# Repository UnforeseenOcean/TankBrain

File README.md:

# TankBrain
Official repository for TankBrain, a replacement board for Academy and other motorized vehicle models

# What is this?
This is an Arduino-compatible* board with remote controller that replaces either the old 30/40MHz band remote control or wired remote on models from Academy Plastic Models or other companies.
Currently it supports Academy's wired motorized tank models (the benchmark being their ROK K1A1 tank model), but with some support it should be easy to make it support nearly all models.

\*: Arduino-compatible in this context means "Arduino IDE compatible". The board in no way, shape or form can support peripherals made for Arduino Uno and other boards.

# Goals
- To create a universal board that fits into most models, including some toy vehicles (such as tanks or cars)
- To make a firmware that handles most functions called by signals through 433MHz ASK/OOK module

# Information
This board currently uses GoodRF SRX887 and STX887 pair, which has a good range of operation with least amount of latency (due to it not containing any signal-to-binary conversion) from the online reviews.

The operating state table is as follows:
```
ABCD (AIN1,AIN2,BIN1,BIN2)
0000 (Stop)
0001 (Backwards Left Strafe)
0010 (Right Strafe)
0011 (Invalid/Unused)
0100 (Backwards Right Strafe)
0101 (Backward)
0110 (Right Turn In Place)
0111 (Invalid/Unused)
1000 (Left Strafe)
1001 (Left Turn In Place)
1010 (Forward)
1011 (Invalid/Unused)
1100 (Invalid/Unused)
1101 (Invalid/Unused)
1110 (Invalid/Unused)
1111 (Brake)
```
Simulation for engine starting and firing is handled by switching the movement state through this table:
```
1010 (Start of "Engine start" movement set)
0101
1010
0101
1010
0101 (Start of "Fire" movement set)
1010
0101
1111
0000 (End)
```
There is a plan to add support for external sound modules (DFPlayer Mini / Serial MP3 player modules)

The board needs some revision and quality/function check, as it has not been made yet. However this is what the board could look like if the current design is made:

Believe it or not this is the second big revision -- the first one was... not good.

# Credits
Pololu - DRV8833 circuit design

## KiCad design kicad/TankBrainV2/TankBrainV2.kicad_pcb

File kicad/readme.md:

# KiCad project files
Yes, they're here. Please make improvements to this, since I have no idea if this is going to do the job or not!

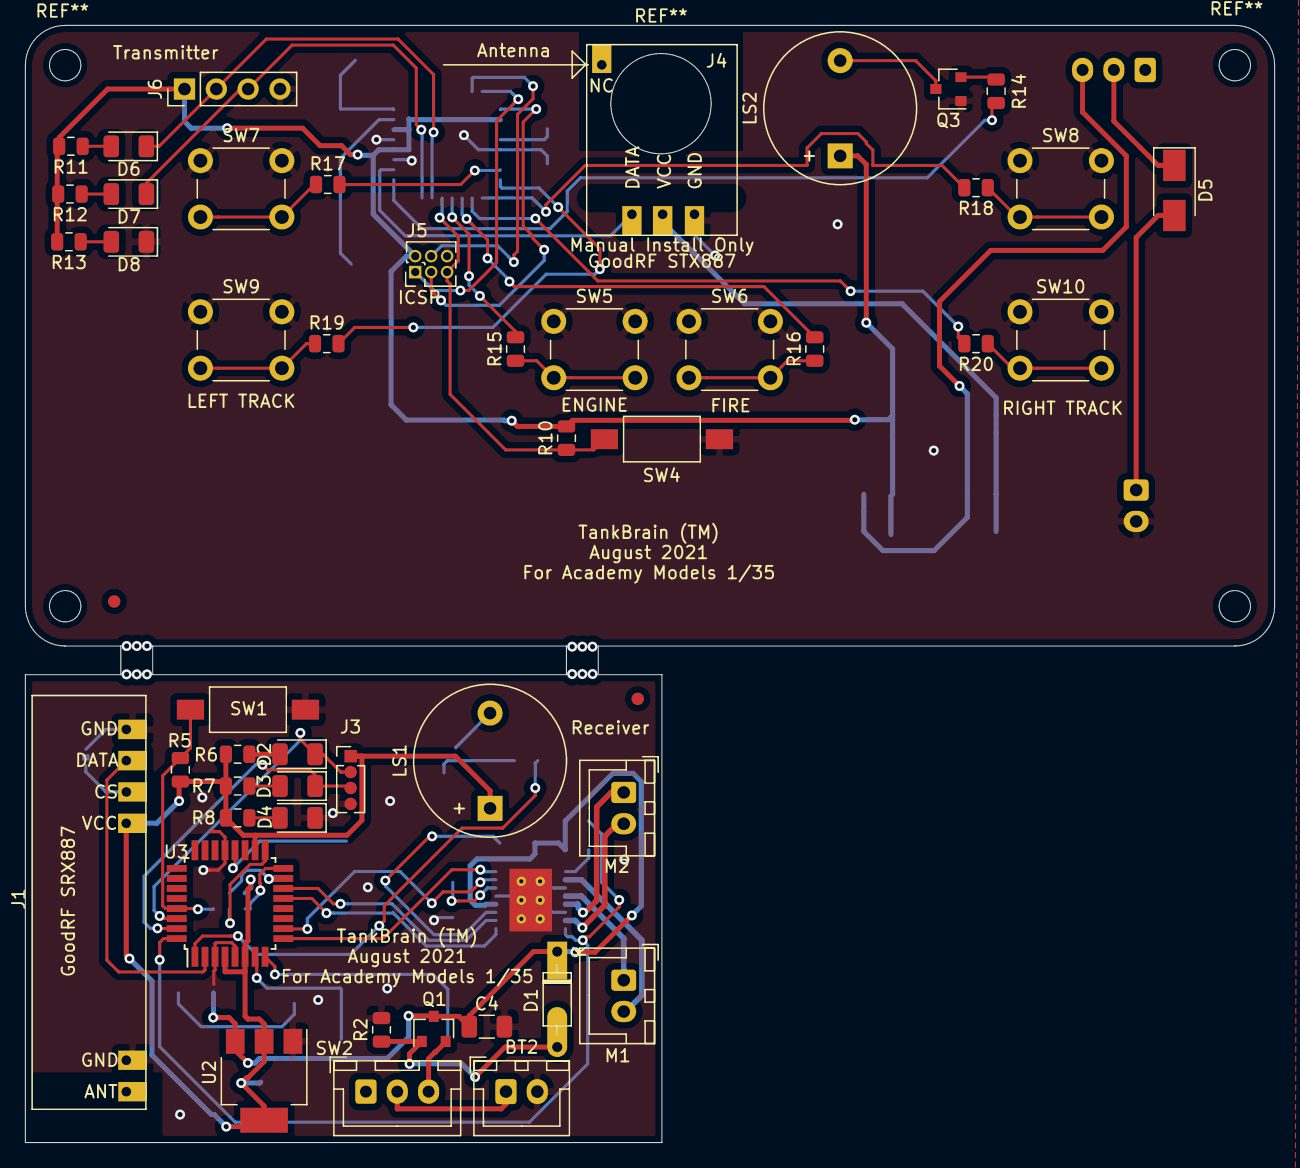
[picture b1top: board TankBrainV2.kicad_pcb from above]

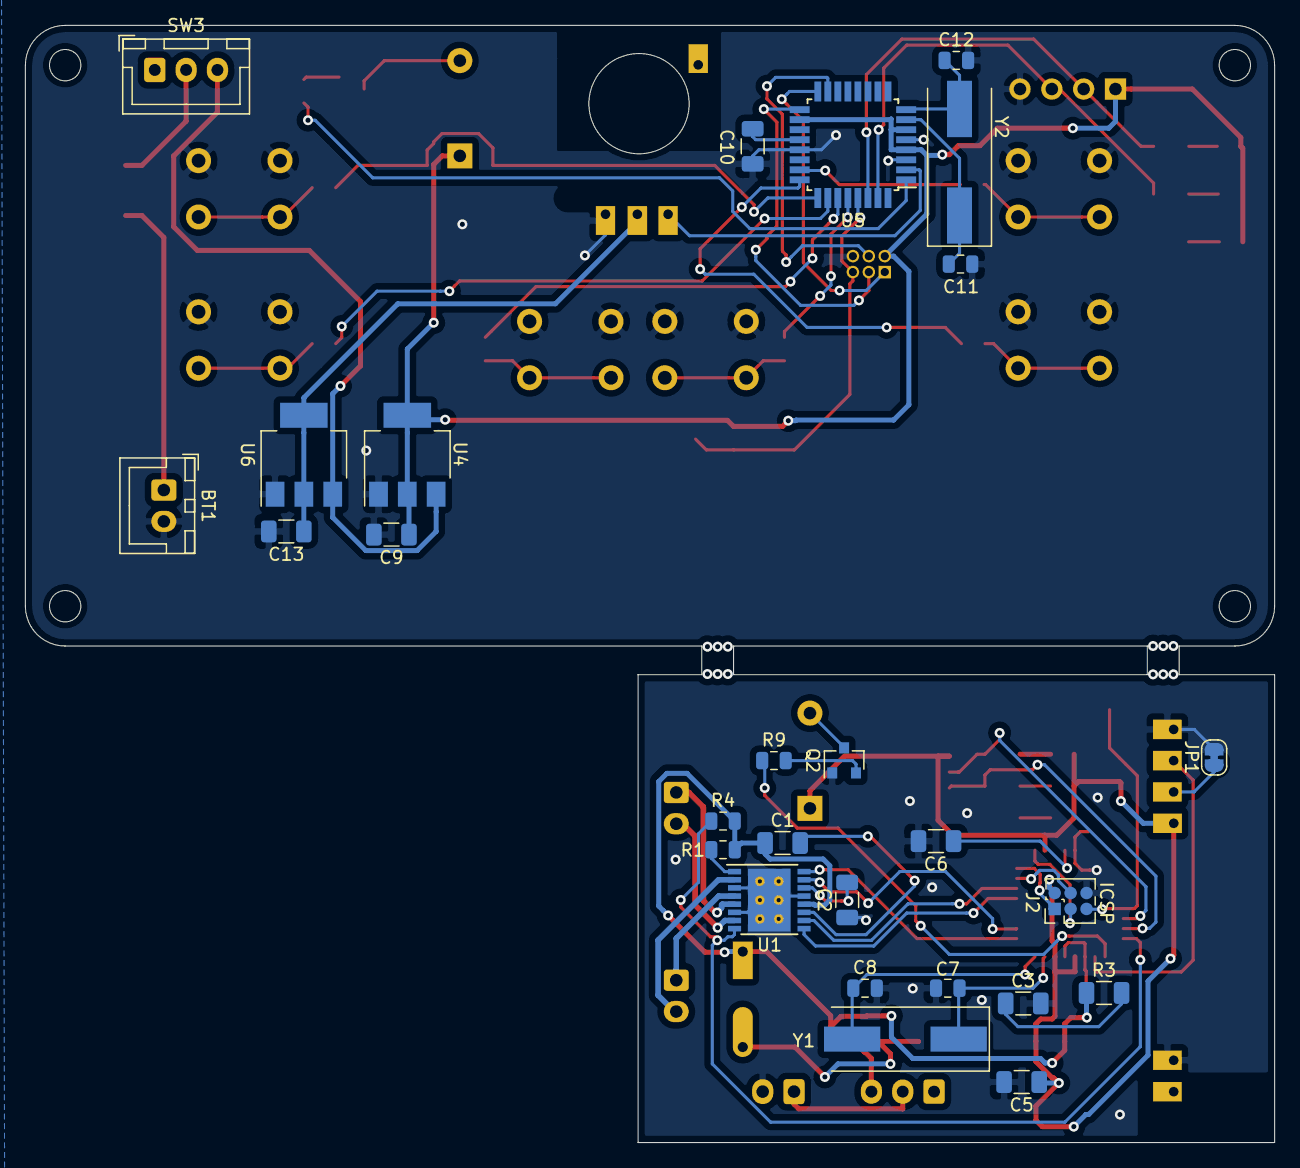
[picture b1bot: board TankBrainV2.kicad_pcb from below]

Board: 2 copper layers, 99.7 x 89.2 mm, 75 parts (27 on the bottom side), 69 nets.

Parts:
BT1: 9V; JST_XH_B2B-XH-A_1x02_P2.50mm_Vertical
BT2: 4.3V; JST_XH_B2B-XH-A_1x02_P2.50mm_Vertical
C1, C4, C5, C6, C9, C10, C13: 100nF; C_1206_3216Metric
C2: 2.2uF; C_1206_3216Metric
C3: 10uF; C_1206_3216Metric
C7, C8, C11, C12: 22nF; C_0805_2012Metric
D1: 6.8V; D_DO-35_SOD27_P7.62mm_Horizontal
D2, D6: RX; LED_1206_3216Metric
D3, D7: TX; LED_1206_3216Metric
D4, D8: PWR; LED_1206_3216Metric
D5: 1N4001; D_SMA
J1: 433RX; SRX887
J2, J5: ISP; PinHeader_2x03_P1.27mm_Vertical
J3: UART; PinHeader_1x04_P1.27mm_Vertical
J4: 433TX; STX887
J6: UART; PinHeader_1x04_P2.54mm_Vertical
JP1: GRF; SolderJumper-2_P1.3mm_Bridged_RoundedPad1.0x1.5mm
LS1, LS2: Speaker; Buzzer_12x9.5RM7.6
M1: L; JST_XH_B2B-XH-A_1x02_P2.50mm_Vertical
M2: R; JST_XH_B2B-XH-A_1x02_P2.50mm_Vertical
Q1: AO3401; SOT-23
Q2, Q3: 2N3904; SOT-23
R1, R4: 47K; R_0805_2012Metric
R2: 100K; R_0805_2012Metric
R3: 1R; R_1206_3216Metric
R5, R10: 10K; R_0805_2012Metric
R6, R7, R8, R9, R11, R12, R13, R14, R15, R16, R17, R18, R19, R20: 1K; R_0805_2012Metric
SW1, SW4: RESET; SW_SPST_FSMSM
SW2: POWER_RX; JST_XH_B3B-XH-A_1x03_P2.50mm_Vertical
SW3: POWER_TX; JST_XH_B3B-XH-A_1x03_P2.50mm_Vertical
SW5: ENGINE; SW_PUSH_6mm
SW6: FIRE; SW_PUSH_6mm
SW7: UP_LEFT; SW_PUSH_6mm
SW8: UP_RIGHT; SW_PUSH_6mm
SW9: DOWN_LEFT; SW_PUSH_6mm
SW10: DOWN_RIGHT; SW_PUSH_6mm
U1: DRV8833PWP; HTSSOP-16-1EP_4.4x5mm_P0.65mm_EP3.4x5mm_Mask2.46x2.31mm_The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
U2, U6: AMS1117-3.3; SOT-223-3_TabPin2
U3, U5: ATmega328P-AU; TQFP-32_7x7mm_P0.8mm
U4: AMS1117-5.0; SOT-223-3_TabPin2
Y1: 8MHz; Crystal_SMD_HC49-SD
Y2: 16MHz; Crystal_SMD_HC49-SD

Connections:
A1: U1.16, U3.9
A2: U1.15, U3.10
B1: U1.9, U3.13
B2: U1.10, U3.14
BUZZER: R9.1, U3.1
BZR: R14.1, U5.1
CK: J5.3, U5.17
ENGINE: R15.2, U5.28
FAULT: R4.1, U1.8, U3.32
FIRE: R16.2, U5.27
GND: BT1.2, BT2.2, C2.1, C3.2, C4.2, C5.2, C6.2, C7.2, C8.2, C9.2, C10.2, C11.2, C12.2, C13.2, D4.1, D8.1, J1.2, J1.6, J2.6, J3.4, J4.4, J5.6, J6.4, JP1.2, Q2.1, Q3.1, R2.2, SW1.2, SW4.2, SW5.1, SW6.1, SW7.1, SW8.1, SW9.1, SW10.1, U1.3, U1.6, U1.13, U1.17, U2.1, U3.3, U3.5, U3.21, U4.1, U5.3, U5.5, U5.21, U6.1
LO1: M1.2, U1.2
LO2: M1.1, U1.4
LSWD: R19.2, U5.24
LSWU: R17.2, U5.23
MI: J5.1, U5.16
MISO: J2.1, U3.16
MO: J5.4, U5.15
MOSI: J2.4, U3.15
unnamed: BT1.1, D5.2
unnamed: C1.2, U1.11
unnamed: C2.2, U1.14
unnamed: C3.1, R3.2
unnamed: C6.1, U3.20
unnamed: C7.1, U3.7, Y1.1
unnamed: C8.1, U3.8, Y1.2
unnamed: C10.1, U5.20
unnamed: C11.1, U5.7, Y2.1
unnamed: C12.1, U5.8, Y2.2
unnamed: C13.1, J4.3, U6.2
unnamed: D1.2, Q1.1, R2.1
unnamed: D2.2, R6.1
unnamed: D3.2, R7.1
unnamed: D4.2, R8.1
unnamed: D5.1, SW3.2
unnamed: D6.2, R11.1
unnamed: D7.2, R12.1
unnamed: D8.2, R13.1
unnamed: J1.4, JP1.1
unnamed: LS1.2, Q2.3
unnamed: LS2.2, Q3.3
unnamed: Q1.2, SW2.3
unnamed: Q2.2, R9.2
unnamed: Q3.2, R14.2
unnamed: R1.1, U1.1
unnamed: R15.1, SW5.2
unnamed: R16.1, SW6.2
unnamed: R17.1, SW7.2
unnamed: R18.1, SW8.2
unnamed: R19.1, SW9.2
unnamed: R20.1, SW10.2
unnamed: SW3.3, U4.3, U6.3
RESET: J2.5, R5.1, SW1.1, U3.29
RF: J1.5, U3.2
RO1: M2.2, U1.7
RO2: M2.1, U1.5
RST: J5.5, R10.1, SW4.1, U5.29
RSWD: R20.2, U5.26
RSWU: R18.2, U5.25
RX: D2.1, J3.2, U3.30
RXQ: D6.1, J6.2, U5.30
SCK: J2.3, U3.17
TX: D3.1, J3.3, U3.31
TXD: J4.2, U5.2
TXQ: D7.1, J6.3, U5.31
VCC: C5.1, J1.3, J2.2, J3.1, LS1.1, R5.2, R6.2, R7.2, R8.2, U2.2, U3.4, U3.6, U3.18
VCCQ: C9.1, J5.2, J6.1, LS2.1, R10.2, R11.2, R12.2, R13.2, U4.2, U5.4, U5.6, U5.18
VD: C1.1, C4.1, D1.1, Q1.3, R1.2, R3.1, R4.2, U1.12, U2.3
VDD: BT2.1, SW2.2

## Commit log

2021-08-30 Rename kicad/TankBrainV2.pro to kicad/TankBrainV2/TankBrainV2.pro
